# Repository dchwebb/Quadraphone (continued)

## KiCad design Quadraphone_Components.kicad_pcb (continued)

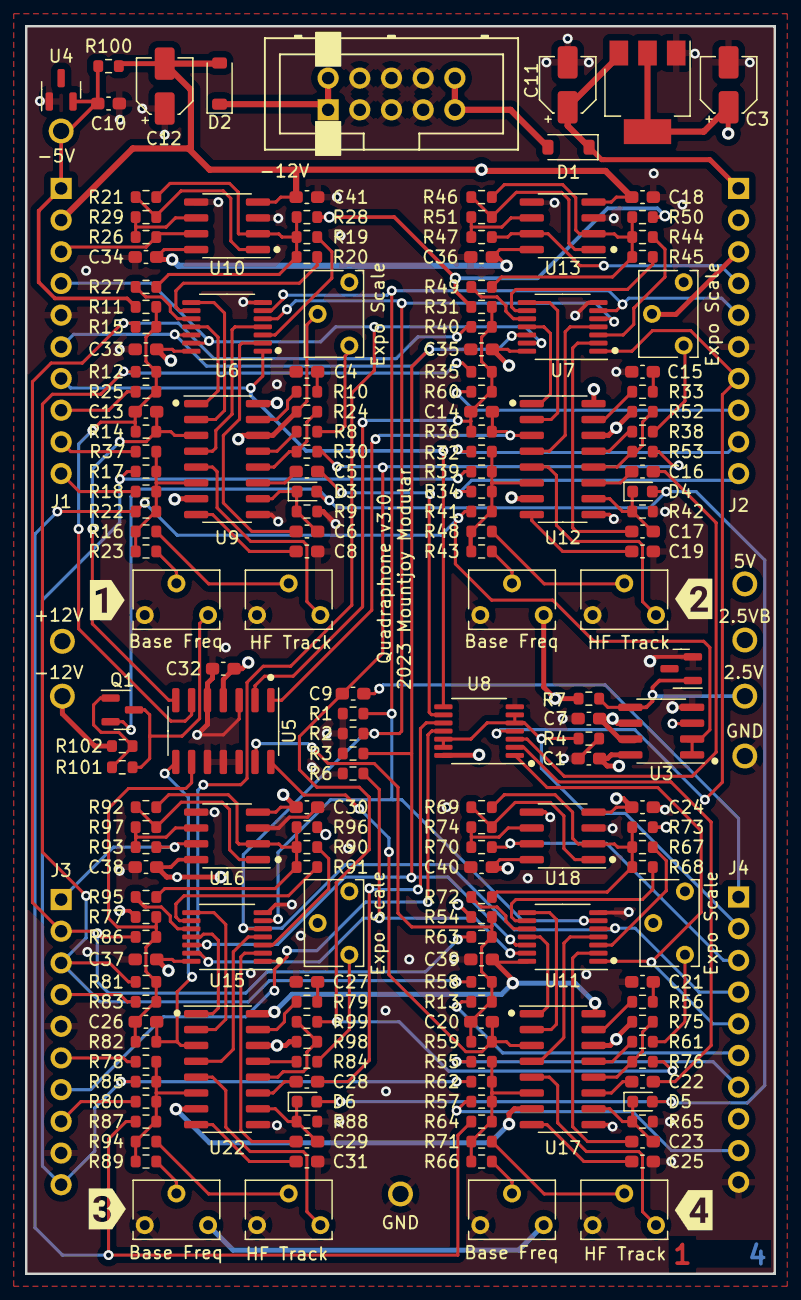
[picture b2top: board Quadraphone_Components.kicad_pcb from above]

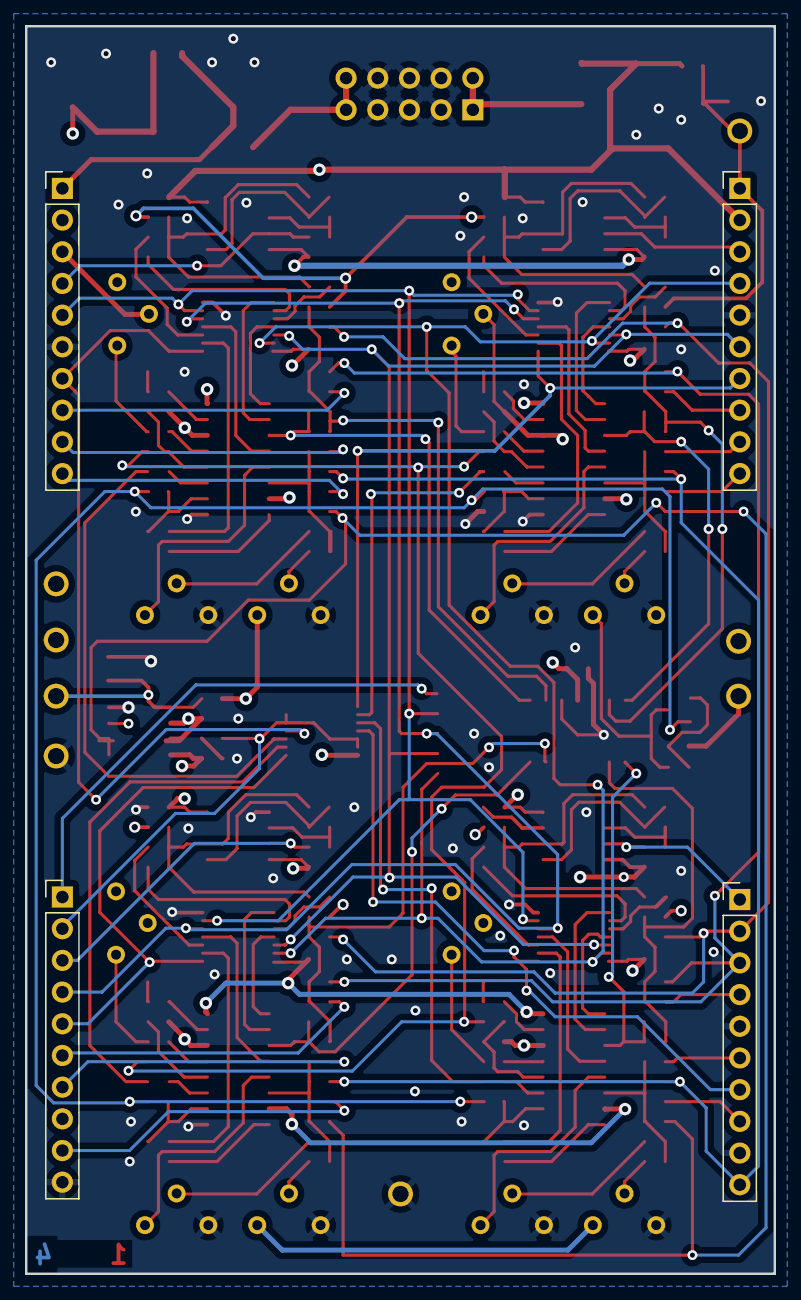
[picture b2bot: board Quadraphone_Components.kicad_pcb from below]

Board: 4 copper layers, 60.0 x 100.0 mm, 196 parts (4 on the bottom side), 143 nets.

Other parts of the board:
kibuzzard-63D3EB0F: G***; kibuzzard-63D3EB0F
kibuzzard-63D3EB2D: G***; kibuzzard-63D3EB2D
kibuzzard-63D3EB3D: G***; kibuzzard-63D3EB3D
kibuzzard-63D3EB53: G***; kibuzzard-63D3EB53

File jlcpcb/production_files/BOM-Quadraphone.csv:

Comment,Designator,Footprint,LCSC
74LV4066PW,"U11,U15,U6,U7,U8",TSSOP-14_4.4x5mm_P0.65mm,C123051
2k7,R7,R_0603_1608Metric,C13167
22uF,C12,CP_Elec_4x5.8,C134793
22uF,C11,CP_Elec_4x5.8,C134798
100nF,"C10,C18,C24,C30,C32,C33,C34,C35,C36,C37,C38,C39,C40,C41",C_0603_1608Metric_Pad1.08x0.95mm_HandSolder,C14663
1uF,"C1,C7,C9",C_0603_1608Metric_Pad1.08x0.95mm_HandSolder,C15849
1nF,"C13,C14,C20,C26",C_0603_1608Metric_Pad1.08x0.95mm_HandSolder,C1588
MMBT3904,Q1,SOT-23,C20526
13k,"R1,R14,R2,R3,R36,R4,R59,R6,R82",R_0603_1608Metric,C22797
1M,"R30,R53,R76,R99",R_0603_1608Metric,C22935
267,"R10,R16,R33,R48,R56,R71,R79,R94",R_0603_1608Metric,C22966
30k,"R19,R20,R27,R44,R45,R49,R67,R68,R72,R90,R91,R95",R_0603_1608Metric,C22984
36k,"R26,R47,R70,R93",R_0603_1608Metric,C23147
49.9k,"R18,R32,R34,R37,R55,R57,R78,R80",R_0603_1608Metric,C23184
510k,"R24,R52,R75,R98",R_0603_1608Metric,C23192
68k,"R22,R41,R64,R87",R_0603_1608Metric,C23231
100k,"R13,R15,R23,R25,R40,R43,R60,R63,R66,R83,R86,R89",R_0603_1608Metric,C25803
10k,"R42,R65,R88,R9",R_0603_1608Metric,C25804
120k,"R12,R21,R28,R35,R46,R50,R58,R69,R73,R81,R92,R96",R_0603_1608Metric,C25808
18k,"R29,R51,R74,R97",R_0603_1608Metric,C25810
47k,"R102,R11,R31,R54,R77",R_0603_1608Metric,C25819
680k,"R17,R39,R62,R85",R_0603_1608Metric,C25822
22k,"R38,R61,R8,R84",R_0603_1608Metric,C31850
20k,R101,R_0603_1608Metric,C4184
2.2k,R100,R_0603_1608Metric,C4190
10nF,"C15,C16,C17,C21,C22,C23,C27,C28,C29,C4,C5,C6",C_0603_1608Metric_Pad1.08x0.95mm_HandSolder,C57112
AMS1117-5.0,U1,SOT-223-3_TabPin2,C6187
TL072,"U10,U13,U16,U18",SOIC-8_3.9x4.9mm_P1.27mm,C6961
MCP6002,U3,SOIC-8_3.9x4.9mm_P1.27mm,C7377
1N5819,"D1,D2,D3,D4,D5,D6",D_SOD-123,C8598

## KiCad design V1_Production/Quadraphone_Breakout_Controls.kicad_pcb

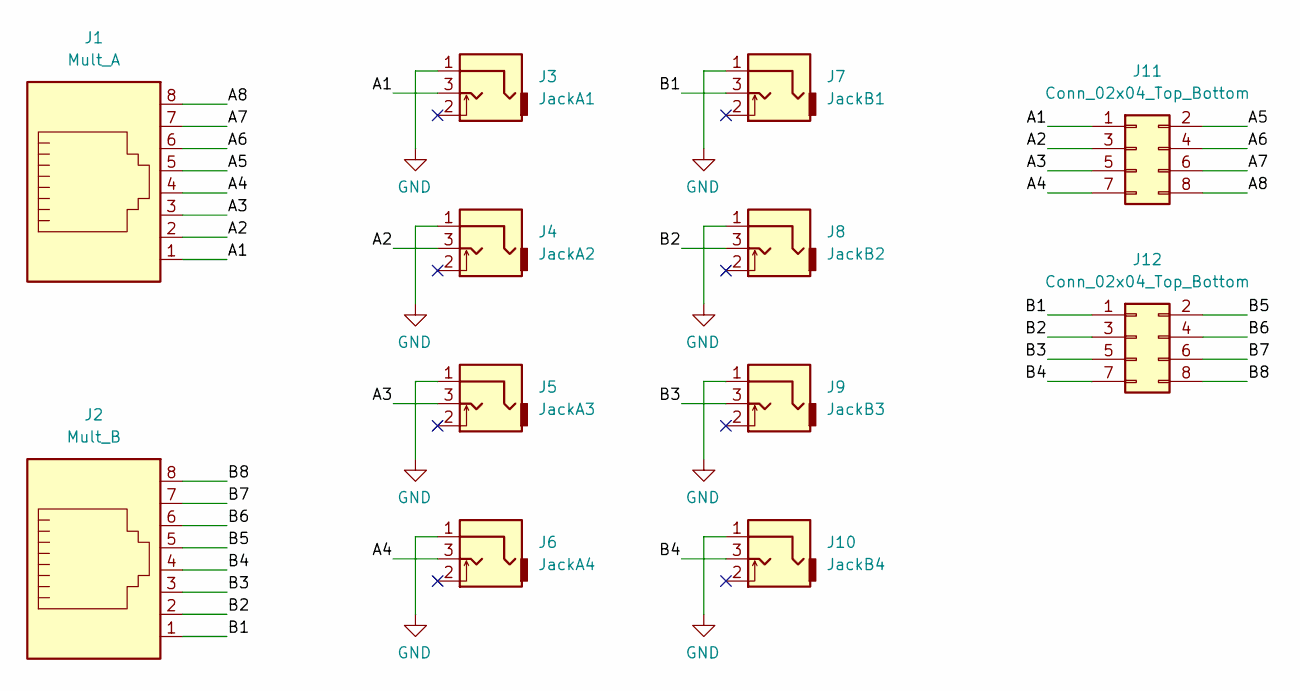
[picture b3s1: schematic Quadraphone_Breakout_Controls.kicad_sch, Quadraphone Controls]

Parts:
J1: Mult_A; RJ45_Molex_42878-8506
J2: Mult_B; RJ45_Molex_42878-8506
J3: JackA1; THONKICONN_hole
J4: JackA2; THONKICONN_hole
J5: JackA3; THONKICONN_hole
J6: JackA4; THONKICONN_hole
J7: JackB1; THONKICONN_hole
J8: JackB2; THONKICONN_hole
J9: JackB3; THONKICONN_hole
J10: JackB4; THONKICONN_hole
J11, J12: Conn_02x04_Top_Bottom; PinHeader_2x04_P2.54mm_Vertical

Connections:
/A1: J1.1, J3.3, J11.1
/A2: J1.2, J4.3, J11.3
/A3: J1.3, J5.3, J11.5
/A4: J1.4, J6.3, J11.7
/A5: J1.5, J11.2
/A6: J1.6, J11.4
/A7: J1.7, J11.6
/A8: J1.8, J11.8
/B1: J2.1, J7.3, J12.1
/B2: J2.2, J8.3, J12.3
/B3: J2.3, J9.3, J12.5
/B4: J2.4, J10.3, J12.7
/B5: J2.5, J12.2
/B6: J2.6, J12.4
/B7: J2.7, J12.6
/B8: J2.8, J12.8
GND: J3.1, J4.1, J5.1, J6.1, J7.1, J8.1, J9.1, J10.1

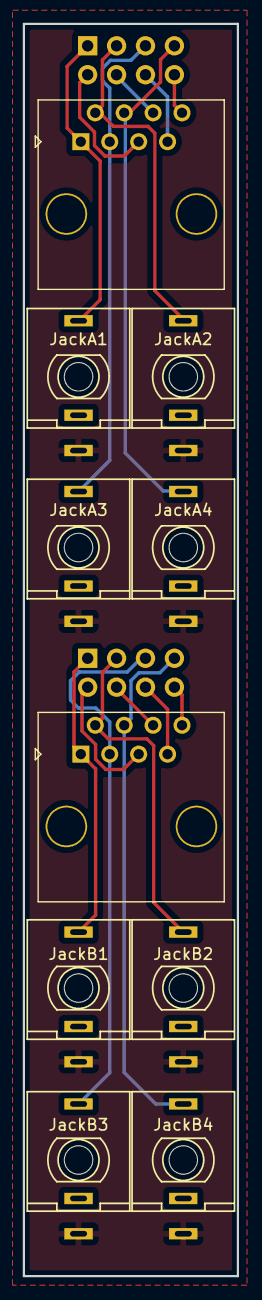
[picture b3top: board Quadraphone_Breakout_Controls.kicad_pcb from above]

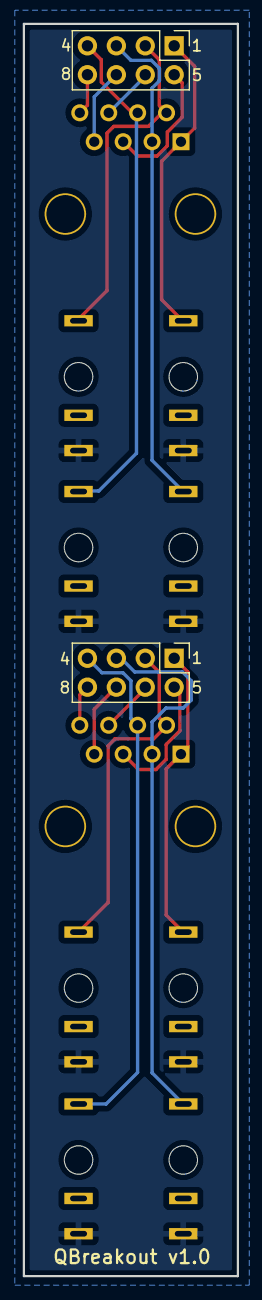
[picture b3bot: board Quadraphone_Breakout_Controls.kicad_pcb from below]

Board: 2 copper layers, 18.8 x 110.0 mm, 12 parts (2 on the bottom side), 17 nets.

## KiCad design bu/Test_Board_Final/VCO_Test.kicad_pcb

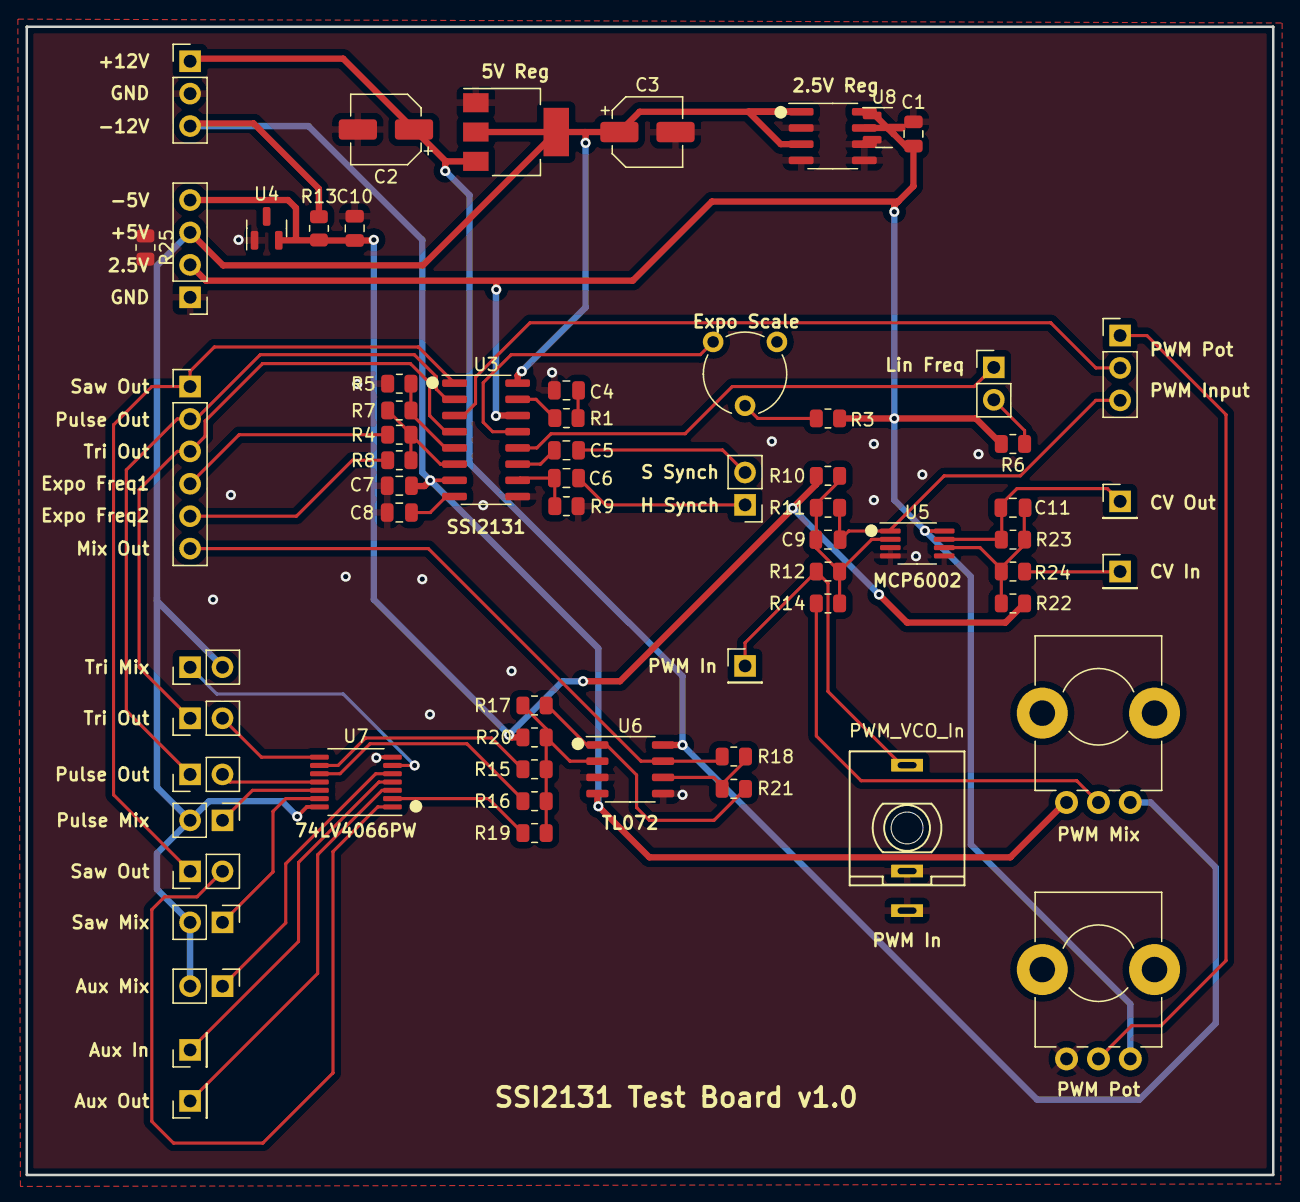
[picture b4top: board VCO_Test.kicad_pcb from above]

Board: 2 copper layers, 97.7 x 90.0 mm, 65 parts (0 on the bottom side), 49 nets.

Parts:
C1: 1nF; C_0805_2012Metric
C2, C3: 10uF; CP_Elec_5x5.7
C4, C5, C6: 10nF; C_0805_2012Metric
C7, C10: 100nF; C_0805_2012Metric
C8: 3.9nF; C_0805_2012Metric
C9, C11: 1.5nF; C_0805_2012Metric
J1: IO; PinHeader_1x06_P2.54mm_Vertical
J2: PWM_VCO_In; THONKICONN_hole
J3: Synch; PinHeader_1x02_P2.54mm_Vertical
J5: AUX_IN; PinHeader_1x01_P2.54mm_Vertical
J6: AUX_OUT; PinHeader_1x01_P2.54mm_Vertical
J7: Power_In; PinHeader_1x03_P2.54mm_Vertical
J8: Power_In; PinHeader_1x04_P2.54mm_Vertical
J9: PWM_IN; PinHeader_1x01_P2.54mm_Vertical
J10: CV_IN; PinHeader_1x01_P2.54mm_Vertical
J11: CV_OUT; PinHeader_1x01_P2.54mm_Vertical
JP1: Freq_Jumper; PinHeader_1x02_P2.54mm_Vertical
JP2: PWM_Jumper; PinHeader_1x03_P2.54mm_Vertical
JP3: Tri_mix; PinHeader_1x02_P2.54mm_Vertical
JP4: Tri_jmp; PinHeader_1x02_P2.54mm_Vertical
JP5: Pulse_mix; PinHeader_1x02_P2.54mm_Vertical
JP6: Pulse_jmp; PinHeader_1x02_P2.54mm_Vertical
JP7: Saw_mix; PinHeader_1x02_P2.54mm_Vertical
JP8: Saw_jmp; PinHeader_1x02_P2.54mm_Vertical
JP9: Aux_mix; PinHeader_1x02_P2.54mm_Vertical
R1, R7: 267; R_0805_2012Metric
R2: 5k; Potentiometer_Piher_PT-6-V_Vertical
R3: 22.1k; R_0805_2012Metric
R4, R8: 49.9k; R_0805_2012Metric
R5: 4k3; R_0805_2012Metric
R6: 499k; R_0805_2012Metric
R9: 10k; R_0805_2012Metric
R10: 47k; R_0805_2012Metric
R11: 13k; R_0805_2012Metric
R12, R24: 100k; R_0805_2012Metric
R13, R25: 2.2k; R_0805_2012Metric
R14, R17, R20: 120k; R_0805_2012Metric
R15, R16, R19: 30k; R_0805_2012Metric
R18: 36k; R_0805_2012Metric
R21: 18k; R_0805_2012Metric
R22: 75k; R_0805_2012Metric
R23: 51k; R_0805_2012Metric
RV1: 5k; Alpha_9mm_Potentiometer_Aligned
RV2: 10k; Alpha_9mm_Potentiometer_Aligned
U1: AMS1117-5.0; SOT-223-3_TabPin2
U2: MCP1501-25xSN; SOIC-8_3.9x4.9mm_P1.27mm
U3: SSI2131; SOIC-16_3.9x9.9mm_P1.27mm
U4: LM4040DBZ-5; SOT-23
U5: MCP6002-xSN; MSOP-8_3x3mm_P0.65mm
U6: TL072; SO-8_3.9x4.9mm_P1.27mm
U7: 4066; TSSOP-14_4.4x5mm_P0.65mm
U8: LM4040DBZ-2.5; SOT-23

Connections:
+2V5: C1.2, J8.2, R3.2, R6.2, R25.2, RV1.1, U2.7 (OUT), U2.8 (FB), U3.14 (VREF), U5.8 (V+), U8.1 (K)
+5V: C3.1, J8.3, JP3.2, JP5.2, JP7.2, JP9.2, R25.1, U1.2 (VO), U2.1 (VDD), U2.3 (~SHDN), U3.16 (VDD), U7.14 (VDD)
+12V: C2.1, J7.1, RV2.1, U1.3 (VI), U6.8 (V+)
-5V: C10.1, J8.4, R10.2, R13.2, R20.2, R22.2, U4.2 (A)
-12V: C7.1, J7.3, R13.1, RV2.3, U3.7 (VSS), U6.4 (V-)
/EXPO_FREQ1: J1.4, R4.1
/EXPO_FREQ2: J1.5, R8.1
/HARD_SYNCH: C6.2, J3.1
/LIN_FREQ: JP1.1, U3.12 (LIN_FREQ)
/MIX_1: R17.1, R21.2, U6.1
/MIX_OUT: J1.6, R18.1, U6.7
/PULSE_MIX: R16.2, U7.10
/PULSE_OUT: J1.2, JP6.1, U3.2 (PULSE_OUT)
/PWM_Ctrl: JP2.2 (C), U3.3 (PWM_CTRL)
/PWM_pot: JP2.1 (A), RV1.2
/PWM_scaled_input: C9.2, JP2.3 (B), R11.1, U5.1
/SAW_MIX: R19.2, U7.2
/SAW_OUT: J1.1, JP8.1, U3.1 (SAW_OUT)
/SOFT_SYNCH: C5.2, J3.2
/TRI_MIX: R15.2, U7.9
/TRI_OUT: J1.3, JP4.1, U3.4 (TRI_OUT)
GND: C1.1, C2.2, C3.2, C4.2, C7.2, C8.1, C10.2, J2.1, J2.2, J7.2, J8.1, R5.1, R9.1, RV1.3, U1.1 (GND), U2.2 (GND), U2.4 (GND), U2.5 (GND), U2.6 (GND), U3.9 (GND), U4.1 (K), U5.3 (+), U5.4 (V-), U5.5 (+), U6.3 (+), U6.5 (+), U7.7 (VSS), U8.2 (A)
unnamed: C4.1, R1.2
unnamed: C5.1, U3.11 (SOFT_SYNC)
unnamed: C6.1, R9.2, U3.10 (HARD_SYNCH)
unnamed: C8.2, U3.8 (TCAP)
unnamed: C9.1, R10.1, R11.2, R12.1, R14.1, U5.2 (-)
unnamed: C11.1, R22.1, R23.2, R24.1, U5.6 (-)
unnamed: C11.2, J11.1, R23.1, U5.7
unnamed: J2.3, J9.1, R12.2
unnamed: J5.1, U7.4
unnamed: J6.1, U7.3
unnamed: J10.1, R24.2
unnamed: JP1.2, R6.1
unnamed: JP3.1, U7.6
unnamed: JP4.2, U7.8
unnamed: JP5.1, U7.12
unnamed: JP6.2, U7.11
unnamed: JP7.1, U7.13
unnamed: JP8.2, U7.1
unnamed: JP9.1, U7.5
unnamed: R1.1, U3.15 (BW_COMP)
unnamed: R2.1, U3.13 (EXPO_SCALE)
unnamed: R2.2, R3.1
unnamed: R4.2, R7.1, R8.2, U3.6 (EXPO_FREQ)
unnamed: R5.2, R7.2, U3.5 (HF_TRACK)
unnamed: R14.2, RV2.2
unnamed: R15.1, R16.1, R17.2, R19.1, R20.1, U6.2 (-)
unnamed: R18.2, R21.1, U6.6 (-)

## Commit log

2022-12-24 Schematic Update
2023-01-05 Voice schematic work; need to do linear FM
2023-01-16 Updates to linear frequency controls
2023-01-16 Split components and control pcbs
2023-01-17 Started PCB layout
2023-01-18 Updated design to use buffered 2.5V reference
2023-01-18 Rough layout of one voice
2023-01-19 Duplicated layout of voices; power supply
2023-01-19 Routed majority of signal traces
2023-01-20 Clean up
2023-01-20 Converted to smaller 4 layer board
2023-01-20 Routing power rails
2023-01-20 Routed 2.5V Power Supply
2023-01-21 Started control board schematic
2023-01-22 Started laying out control board
2023-01-23 Started laying out Panel
2023-01-24 Rough Layout of Panel
2023-01-25 First draft panel done
2023-01-26 Refinements to panel and controls
2023-01-27 Fixed ground connections on component board
    Added JLC PCB plug-in
    Schematic clean-up
2023-01-27 Added RJ45 breakout module
2023-01-29 Prepared all gerbers
2023-01-31 Fixed issue with hole for voice switch size
2023-02-20 Updates for v2 on control board
2023-03-03 Clean up control board
2023-03-22 Added readme
2023-03-22 Spelling fix in graphics
2023-03-29 Fixes to footprints on controls board
2023-04-04 v2.0 Update with Synch pulse at start to fix oscillators not starting
2023-04-05 Completed layout of synch pulse modification
2023-04-16 Updated production files for version 2 (Start up pulse)
2023-04-28 Added alternative control pcb layout with 3 way switch for octave
2023-04-30 Create gerbers for control board changes;
    Notes for potential v3 component revision
2023-05-28 Started Rev 3 with buffered octave control
2023-08-12 Updates to v3; changed output mix feedback resistors to lower output level
2023-08-14 Updates for v3 production
2023-08-15 Updates to controls Synch input protection
2023-08-17 Updated resistor values in VCO tuning circuits
2023-08-21 Gerbers Prepared and Ordered
2023-09-14 Minor changes
